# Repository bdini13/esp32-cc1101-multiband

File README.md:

# ESP32 + CC1101 Multiband

A custom USB-C development board combining an **ESP32-WROOM-32E-N8** with an
integrated **CC1101** sub-GHz radio, software-selected RF paths, and a vertical
SMA antenna connector at the opposite end from USB-C.

**Rev A3 · Fully connected review candidate · Not approved to manufacture or sell**

The aim is to replace a separate ESP32 board, CC1101 breakout and jumper wires
with one purpose-built PCB. The first intended build is **five assembled
engineering prototypes**, after the pre-order checks are complete. Possible
product sales are a future option, not a launch announcement.

## Current design

*KiCad design render—not a photograph of a built board. USB, SMA and some
RF parts lack complete 3D bodies. Their absence in the image does not mean
they were removed from the design.*

<details>
<summary>Top view and experimental routing</summary>

*The routing image is a separate experimental candidate, not the main placement
file or a fabrication package. Bottom and inner routes are not shown here.*

</details>

[Schematic SVG](output/svg-A3/esp32-cc1101-multiband.svg) ·
[Latest design report](reports/autonomous-refinement-A3-2026-09-26.md) ·
[Draft BOM](hardware/bom-draft.csv) · [Roadmap](ROADMAP.md)

Latest work: A3 replaces the power supply and RF switches, completes routed
connectivity, adds safe RF boot sequencing and proposes all populated parts.
See [engineering decisions and first-power instructions](docs/06-A3-prototype-engineering.md)
and the [pre-order blocker report](reports/preflight-A3.json). The crystal was
relocated and rerouted: all 180 artifact checks and six route screens now pass.
Independent/supplier reviews remain pending. No hardware has been tested.
Do not order historical A2 files.

## Building blocks and design inputs

### ESP32-WROOM-32E-N8 — controller and 2.4 GHz connectivity

*Stock module reference image: Espressif, linked from the manufacturer's site.
This is not a photo of the custom board or a guarantee of the N8 marking.*

The actual component is an Espressif module, not an entire stock development
board soldered onto another PCB. The selected N8 variant has 8 MB flash; its
ESP32 provides a dual-core processor, 2.4 GHz Wi-Fi and Bluetooth. Its PCB
antenna is separate from the sub-GHz SMA path. The antenna section extends
beyond the custom base board to preserve its keepout.
[Module datasheet](https://documentation.espressif.com/esp32-wroom-32e_esp32-wroom-32ue_datasheet_en.html).

Power/programming uses ESP32 development-board conventions: USB-to-UART,
automatic reset/boot control and manual BOOT/RESET buttons. This is not a
pin-compatible clone of a particular commercial DevKit.
[Espressif ESP32-DevKitC reference](https://docs.espressif.com/projects/esp-dev-kits/en/latest/esp32/esp32-devkitc/user_guide.html).

### Texas Instruments CC1101 — sub-GHz transceiver

*Representative package image: Texas Instruments. This is the IC package,
not a complete CC1101 antenna module; package markings may differ.*

The PCB integrates **CC1101RGPR** directly, with its crystal, bypass capacitors,
balun, switches and matching/filter components. TI specifies tuning ranges
of 300–348, 387–464 and 779–928 MHz. That does **not** make every frequency or
antenna equally usable or establish this board's RF performance.
[CC1101 product information and datasheet](https://www.ti.com/product/CC1101).

The separate [Amazon CC1101 module](https://a.co/d/01gplHzS) supplied by the
owner was a functional starting point. Its exact internal circuit and advertised
four-band performance have not been independently verified here. The switched
RF topology and initial component values also reference the
[M5Stack Cap CC1101 schematic](https://docs.m5stack.com/en/cap/Cap_CC1101).
This is a different implementation, not an endorsed M5Stack product.

### Supporting parts currently selected

| Function | Current design choice |
|---|---|
| USB-C | HRO TYPE-C-31-M-12, USB 2.0 connection |
| USB-to-UART | Silicon Labs CP2102N-A02-GQFN24 |
| 3.3 V regulator | AP63203WU-7 buck, XAL4030 4.7 uH inductor |
| USB startup / UART isolation | TPS22918, SN74LVC2G125; J4 ships unjumpered |
| Radio reference | Abracon ABM8, 26 MHz; load requires validation |
| RF selection | Two pSemi PE42442A-Z SP4T switches; three paths used |
| RF balun | B0310J50100AHF |
| Antenna connector | Amphenol 132134, vertical standard SMA female, 50 ohm |

See [third-party notices](THIRD_PARTY_NOTICES.md) for provenance, image credits
and license boundaries. Parts remain subject to sourcing, footprint and assembly
approval; the BOM is not an approved shopping list.

## Planned capabilities and features

| Feature | Planned behavior | Status |
|---|---|---|
| Four target bands | 315 / 433 / 868 / 915 MHz, one selected at a time | Not RF-validated |
| Software band switching | GPIO-operated RF switches; no DIP switches | Circuit present; firmware isolation only |
| Three RF branches | Dedicated 315 and 433 paths; shared 868/915 path | Matching, loss and isolation unmeasured |
| Single sub-GHz SMA | Vertical connector opposite USB-C | Placed; mechanical approval pending |
| USB-C power/programming | 5 V input, USB-to-UART flashing/logging | Captured; not bench-tested |
| Wi-Fi / Bluetooth | Available through the ESP32 module | Application integration planned |
| Developer controls | BOOT, RESET, LEDs and test pads | Included in draft |
| Expansion | Optional DNP 10-pin header | Included in draft |
| PCB | 90 × 36 mm base, four layers, nominal 1.6 mm | Stackup/impedance release pending |
| Safe bring-up | RF paths isolated; no transmit command | Implemented in initial firmware |

Band switching changes the **hardware path**. Future firmware must also set the
radio frequency/modem registers and operating limits. One CC1101 cannot listen
on all four bands simultaneously. Use an antenna suitable for the selected
band; a shared SMA does not imply a universal antenna.

There is no native USB, USB-PD, battery charger, finished RF application or
guaranteed protocol compatibility in this revision.

## What has actually been checked?

Snapshot: **2026-09-26**, KiCad 10.0.6. Design-file checks, not lab results.

| Check | Result |
|---|---|
| Schematic ERC | 0 reported violations |
| Main placement seed DRC | 0 violations; 283 unconnected items (not the routed board) |
| Targeted artifact checks | **180 / 180 passing** on refined candidate / explicit seed checks |
| Added route screens | **6 / 6 passing**; oscillator routing, cross-layer clearance and modeled DC drops |
| Separate A3 routed candidate DRC | **0 violations; 0 unconnected items** |
| Fresh schematic / routed PCB comparison | Every numbered pad net, value and footprint name matches |
| Layer constraints | No signal traces on In1; RF/clock top-only; documented USB crossover |
| Candidate power routing | Main rails explicitly routed; 60 narrower branch/neck segments listed; critical copper paths quantitatively screened |
| Parts selection | **94 / 94** populated positions have proposed exact parts; sourcing unapproved |
| Physical boards tested | **None** |

Zero reported violations does not prove working or compliant hardware. A3's
power redesign addresses the earlier LDO heat problem and the new switches
cover the target bands in their specified frequency range. Actual power
sequencing, temperature, impedance, matching and crystal startup/frequency
remain unmeasured. C21 and U5 contain in-pad vias requiring filled/capped
processing; supplier DFM confirmation is mandatory. USB power must be
configured before fitting J4, and full combined Wi-Fi/radio load is not approved.

[Raw reports](reports/) · [Verification checklist](docs/04-verification-plan.md) ·
[Power, routing and RF validation plan](docs/06-A3-prototype-engineering.md)

## Roadmap

1. **Design capture — substantially complete:** schematic, placement, draft
   BOM, local footprints, bring-up firmware and automated checks.
2. **Prototype review — in progress:** routed connectivity and proposed parts
   complete; crystal, power, mechanical, supplier and independent review open.
3. **Five-board build — not ordered:** reviewed fabrication and assembly files,
   then separately approved prototype procurement.
4. **Bench and RF tuning — not started:** power/temperature, USB, crystal,
   per-band matching, harmonics and receive performance.
5. **Firmware/application — planned:** validated receive-first operation,
   controlled band changes and deliberately configured regional limits.
6. **Possible product — undecided:** hardware revision, compliance, enclosure,
   test fixtures, sourcing, support and commercial terms.

The [detailed roadmap](ROADMAP.md) uses acceptance criteria, not promised dates.
There is no release date, sales price, preorder or claim of certification.

## Open the project

Open `hardware/esp32-cc1101-multiband.kicad_pro` in **KiCad 10** for the main
placement seed and schematic. Open `hardware/A3-routing-candidate.kicad_pro`
separately for the unapproved routing experiment. Do not order either one.

Python generators are the editable source for this checkpoint. **Regenerating
placement overwrites the generated board; preserve manual routing first.**
See [rebuild instructions](hardware/REBUILD.md) and
[firmware instructions](firmware/bringup/README.md).

Initial firmware resets the CC1101, checks repeated PARTNUM/VERSION reads and
stable IDLE state, and logs explicit failures. It does not configure a receiver
or transmitter and has not run on physical hardware. Passing digital diagnostics
is not proof of authenticity or RF qualification.

## AI disclosure

This project is developed with substantial assistance from **OpenAI Codex**
under the owner's direction. AI assisted with component research, schematic/PCB
generators, footprints, experimental routing, firmware, documentation and review.
Design images are KiCad renders/exports, not AI-generated product photographs.

AI output and automated checks can contain errors. They are not independent
engineering approval, bench validation or regulatory certification. No physical
prototype has been completed. Qualified human electrical/RF review remains a
release gate. See the [full AI disclosure](AI_DISCLOSURE.md).

## Licensing, commercial plans and safety

This initial publication uses the **[Public Review License](LICENSE)**:
non-commercial study/private evaluation is permitted; manufacturing, product
sales and other uses beyond its limited permissions require written permission.
Commercial rights are reserved while the owner's plans are undecided. This is
**source-available, not open-source/open hardware**. Third-party terms are
separate; see [notices](THIRD_PARTY_NOTICES.md). Obtain legal advice before
relying on the custom license for a commercial launch.

Use only with equipment and signals you own or are authorized to test. Tunable
frequencies are not automatically permitted transmit frequencies. Final use and
sale require applicable RF, EMC, product-safety and other compliance work. This
prototype is not for safety-critical applications. No manufacturer named here
endorses the project.

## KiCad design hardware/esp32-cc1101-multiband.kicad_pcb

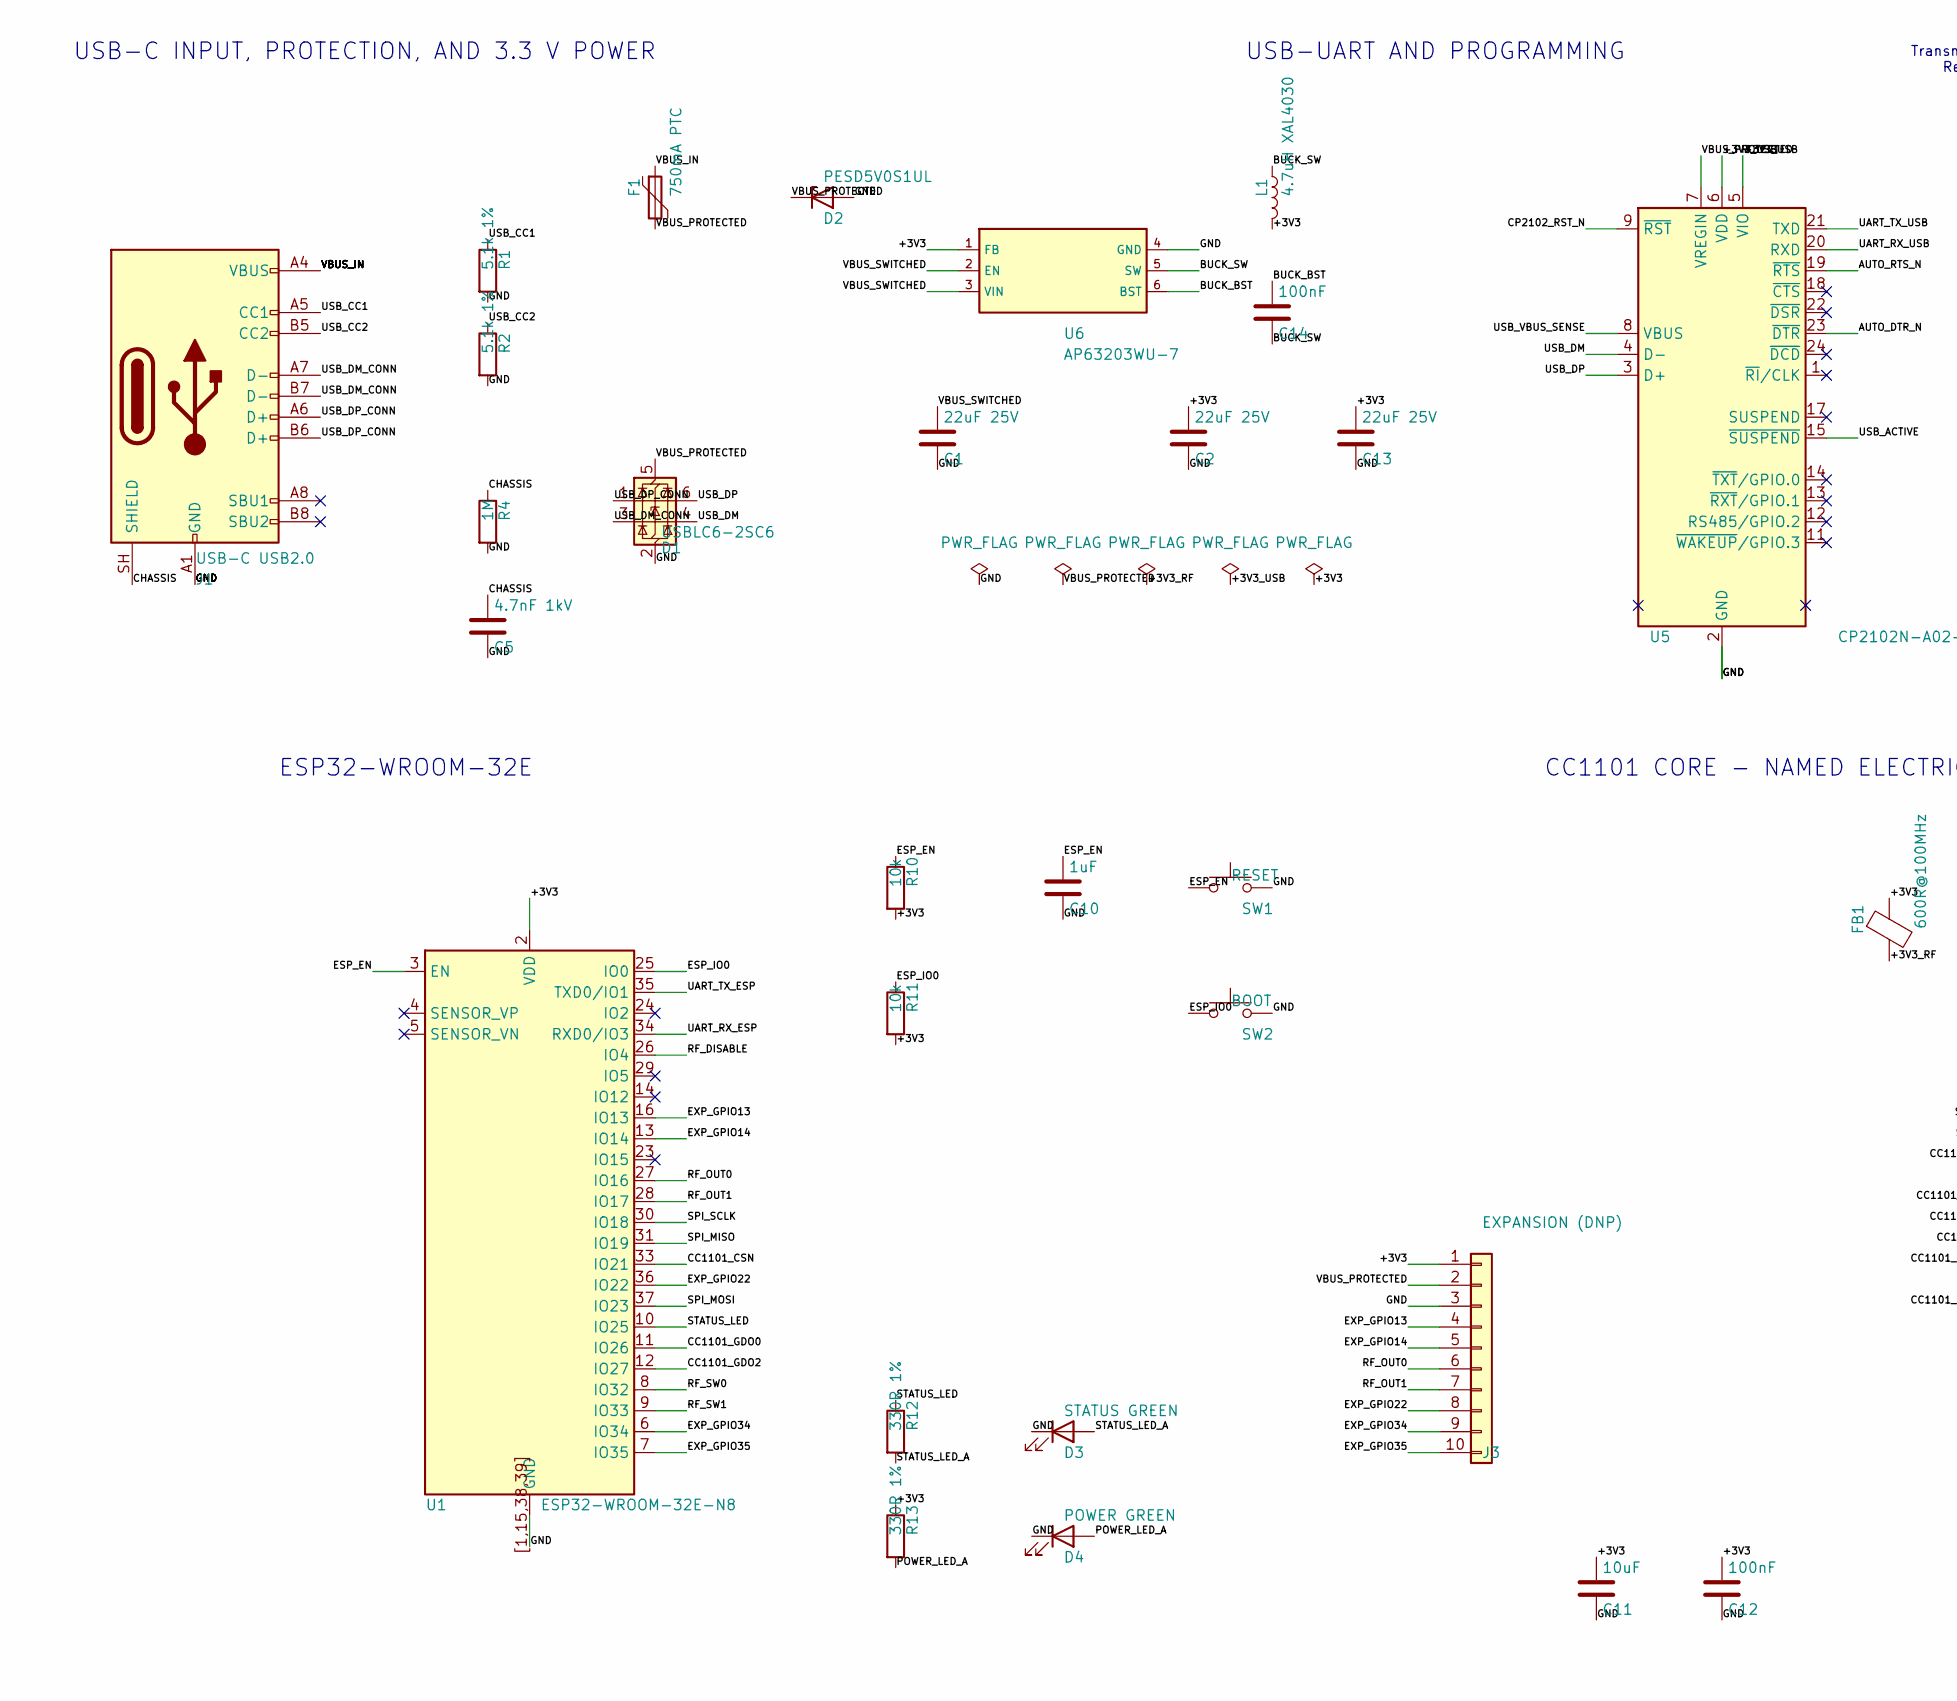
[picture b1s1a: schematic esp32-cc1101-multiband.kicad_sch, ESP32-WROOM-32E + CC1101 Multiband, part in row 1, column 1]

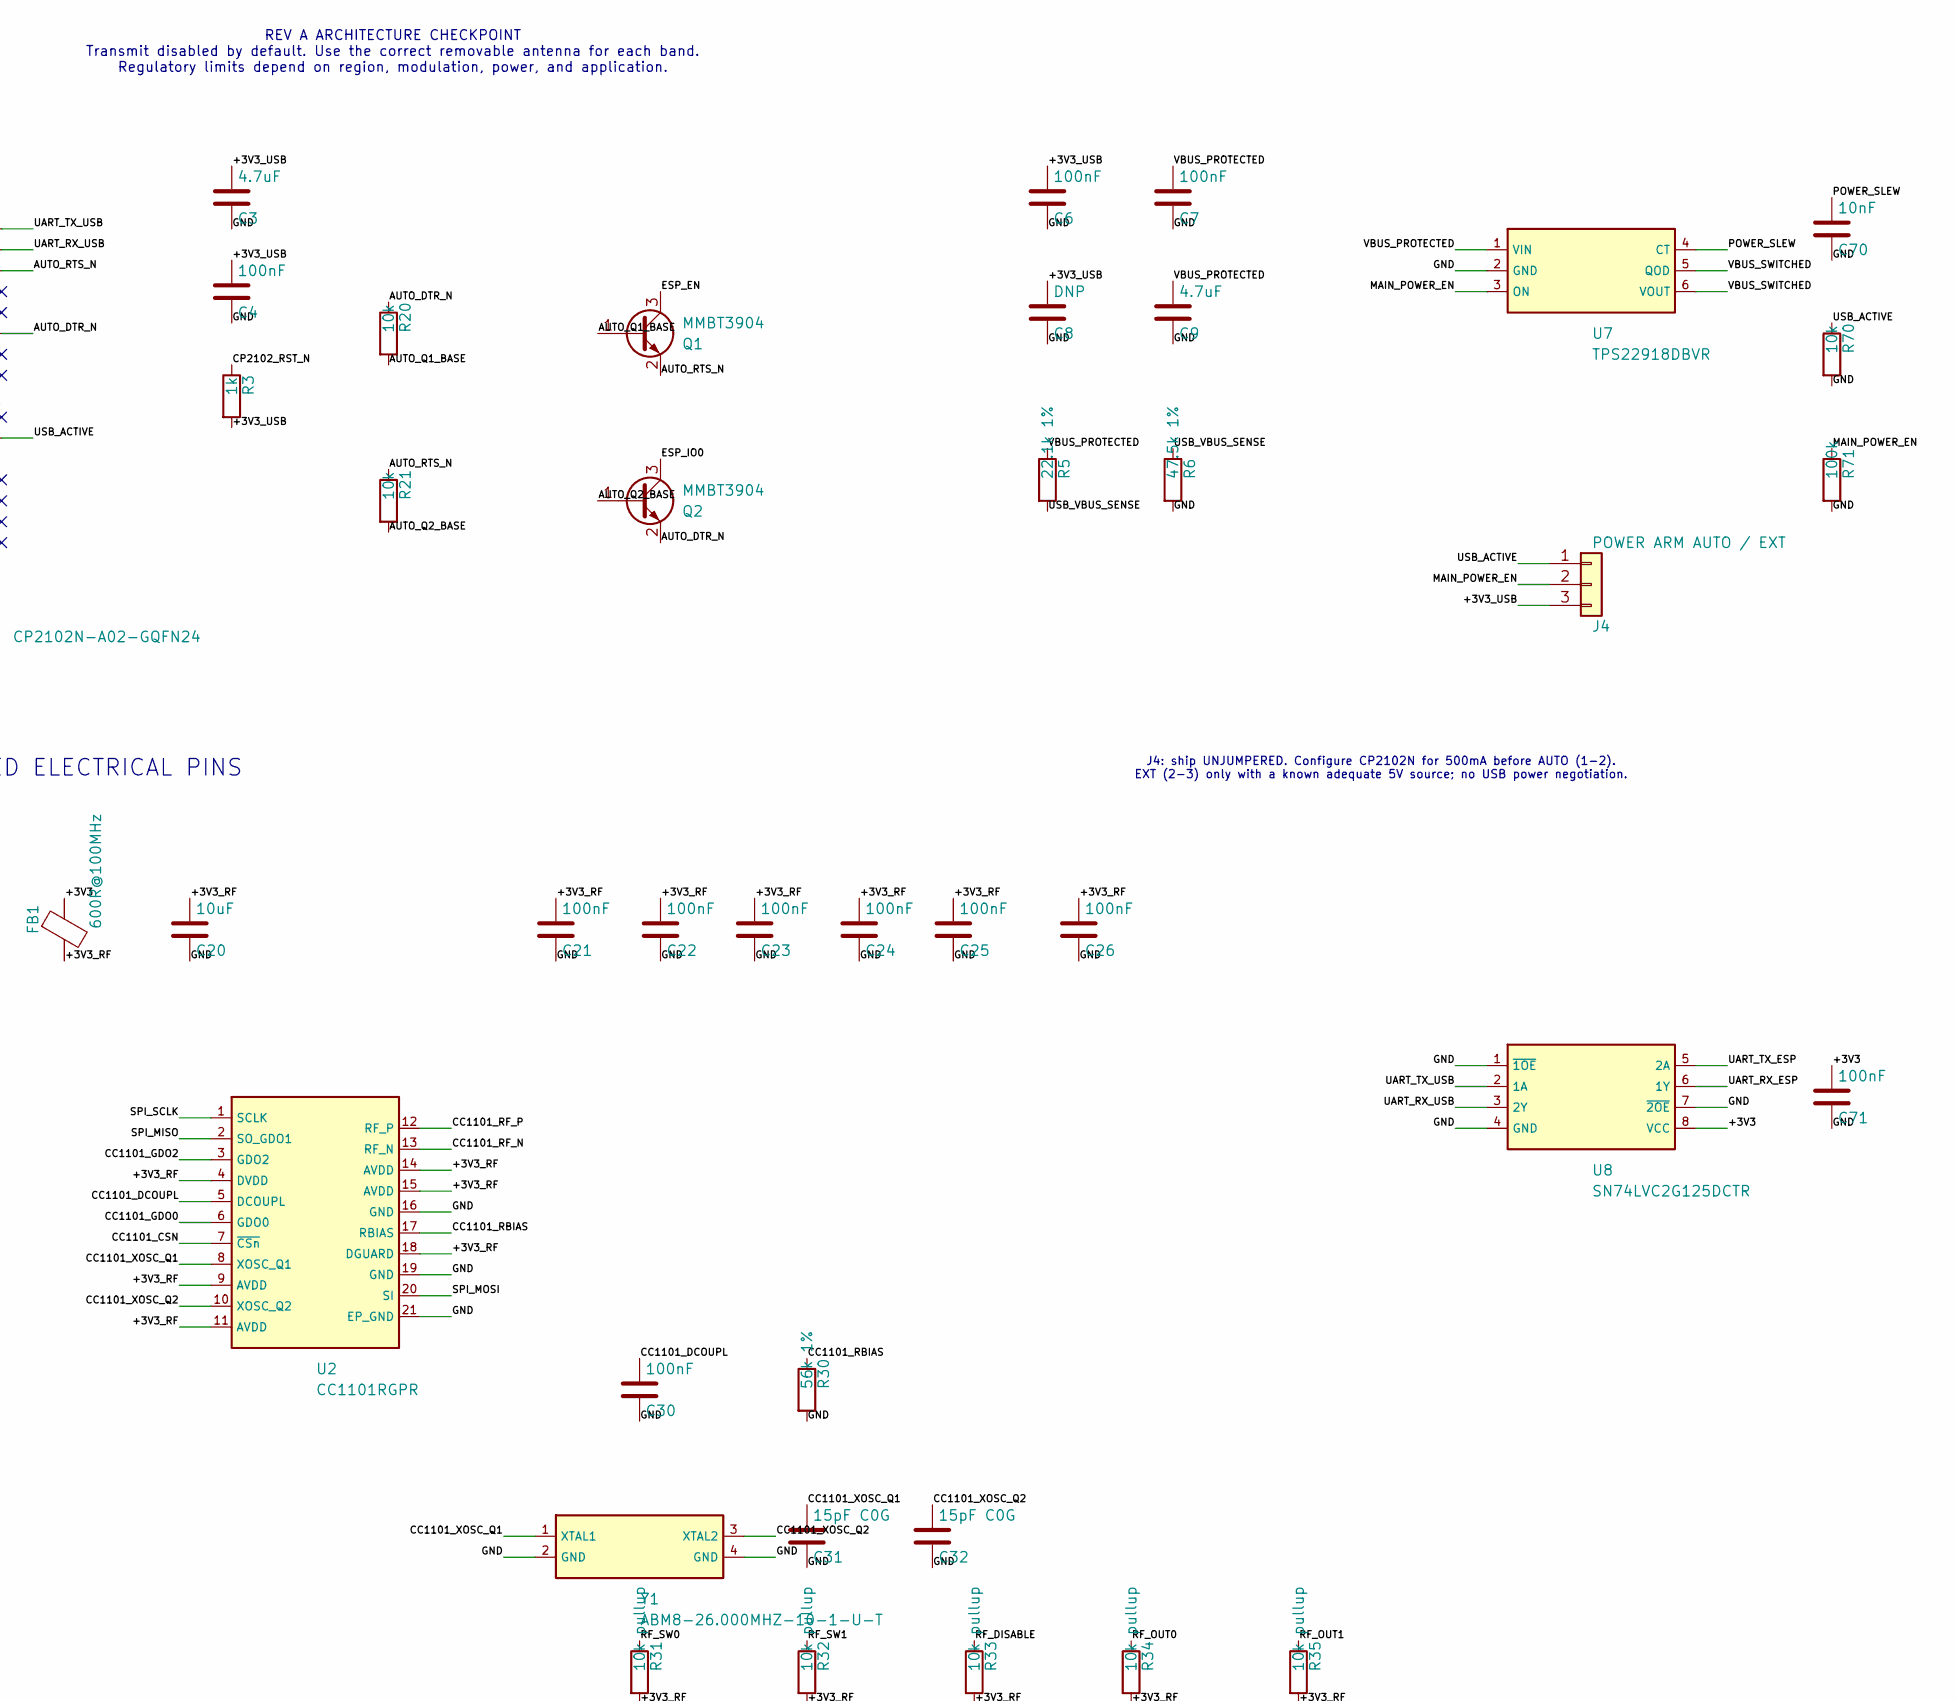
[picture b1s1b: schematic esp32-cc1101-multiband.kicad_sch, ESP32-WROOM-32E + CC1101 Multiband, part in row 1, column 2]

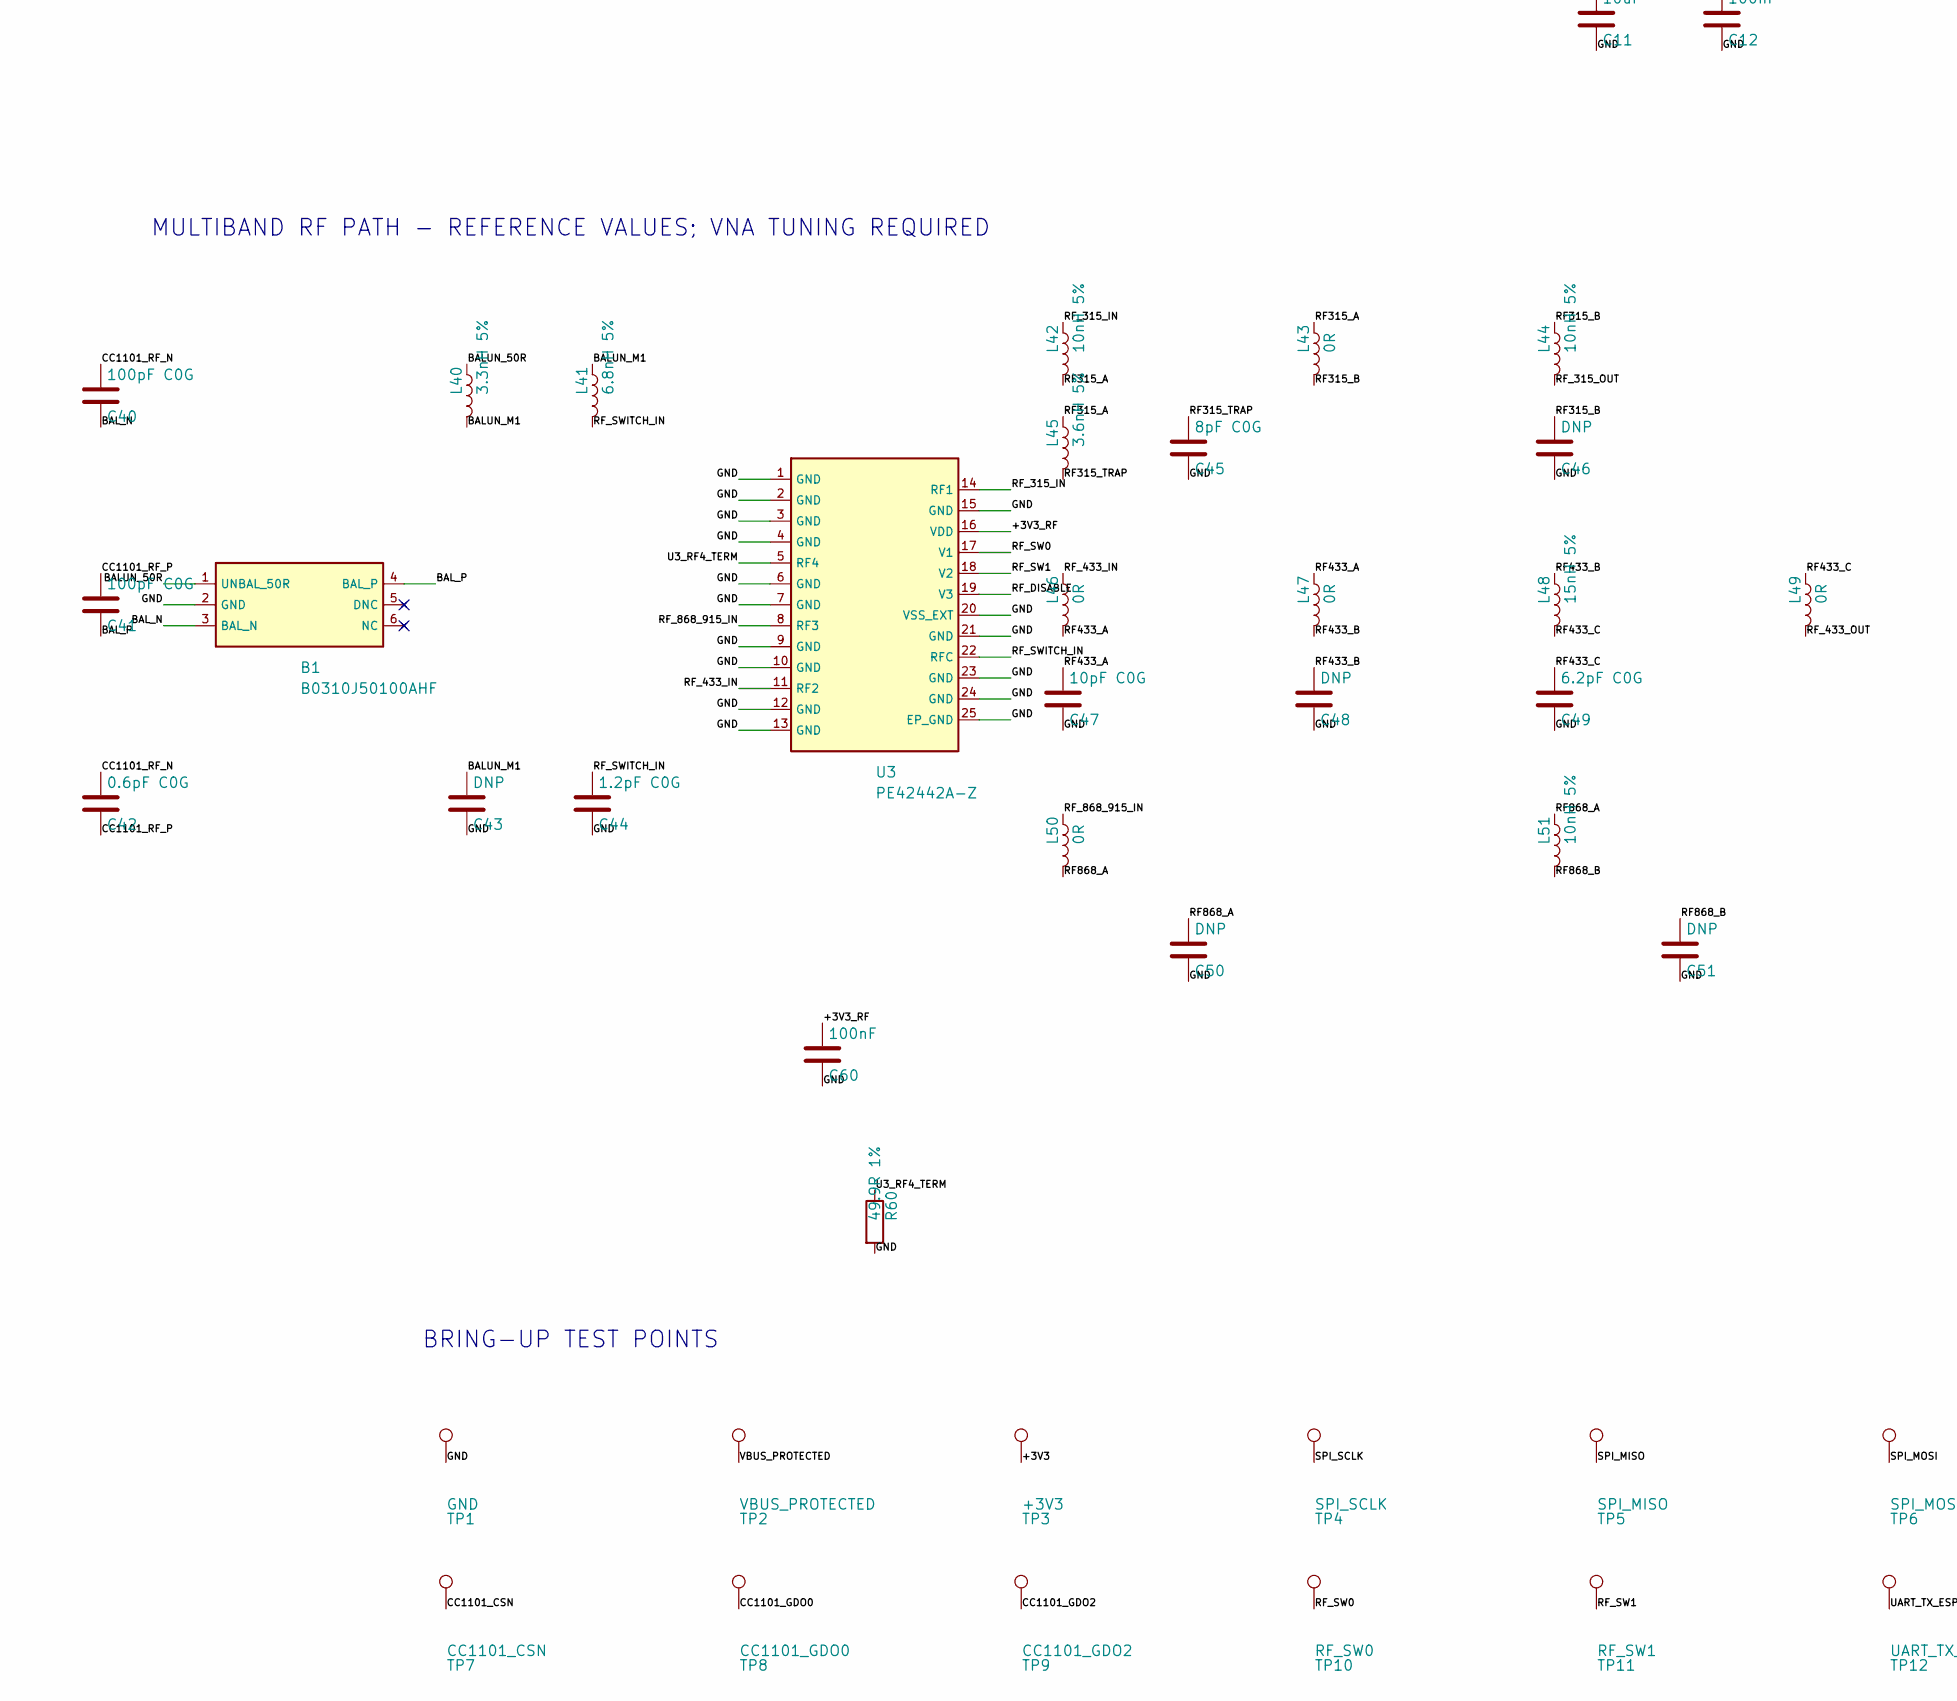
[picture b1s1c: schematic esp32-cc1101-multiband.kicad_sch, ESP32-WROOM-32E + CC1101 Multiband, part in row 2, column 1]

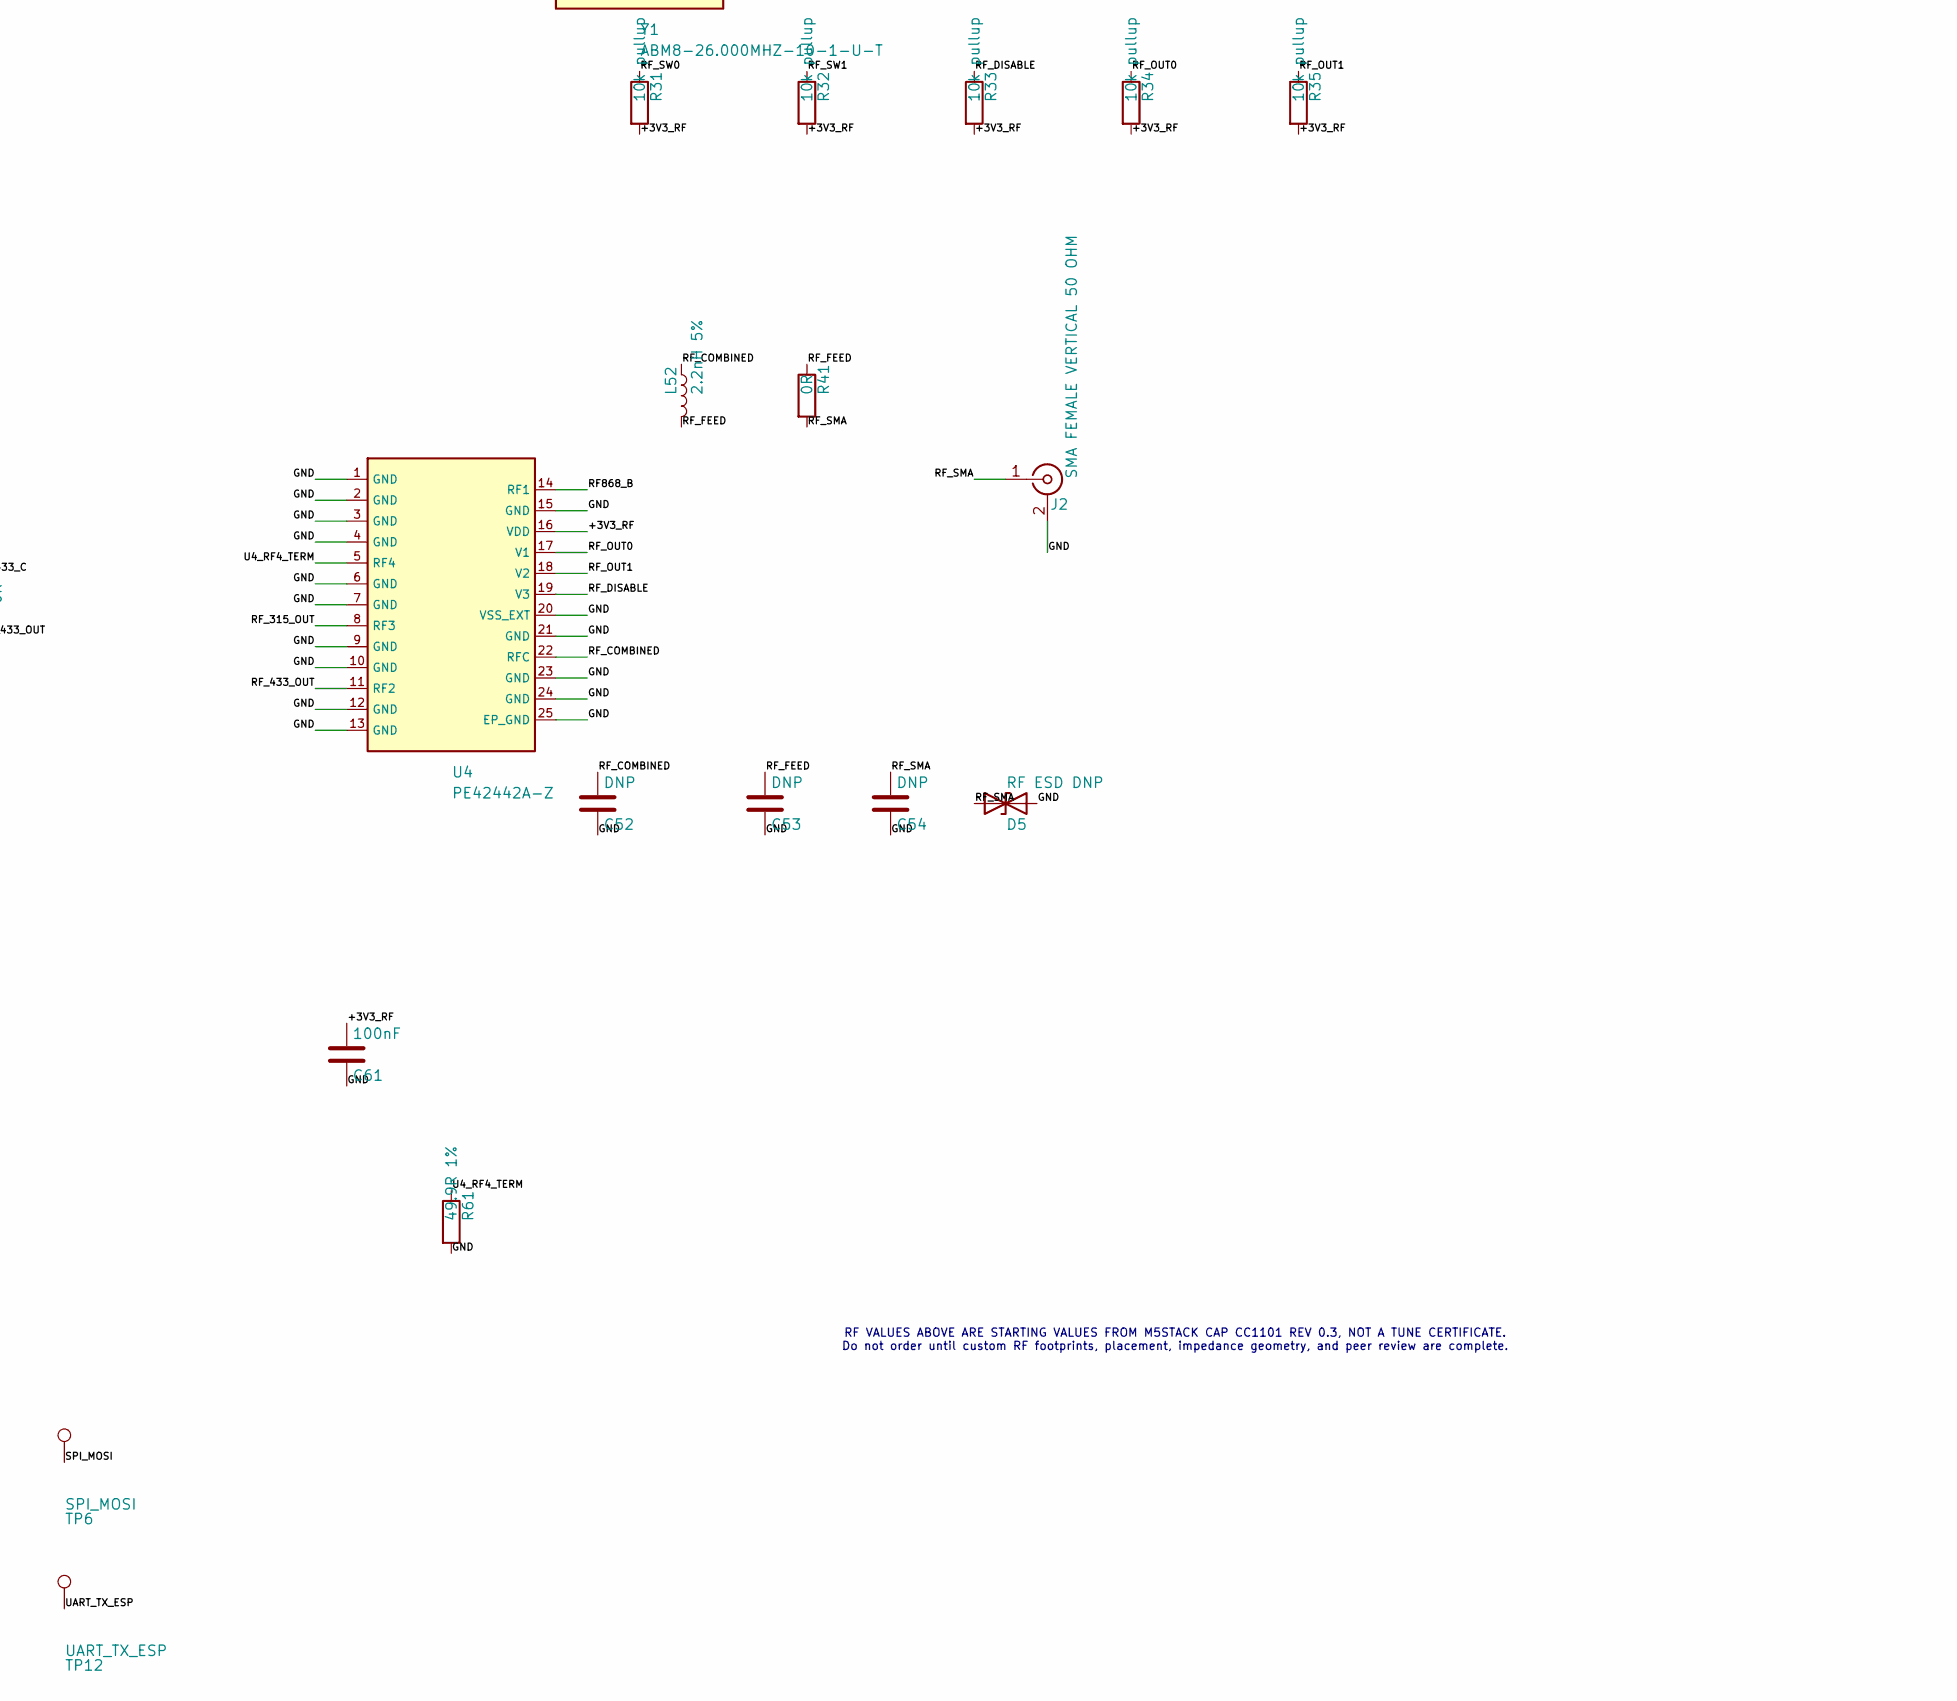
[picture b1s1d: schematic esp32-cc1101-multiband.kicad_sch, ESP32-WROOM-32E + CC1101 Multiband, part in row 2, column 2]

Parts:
B1: B0310J50100AHF; TTM_B0310J50100AHF
C1, C2, C13: 22uF 25V; C_1206_3216Metric
C3, C9: 4.7uF; C_0603_1608Metric
C4, C6, C7, C12, C14, C21, C22, C23, C24, C25, C26, C30, C60, C61, C71: 100nF; C_0402_1005Metric
C5: 4.7nF 1kV; C_1206_3216Metric
C8: DNP; C_0603_1608Metric
C10: 1uF; C_0603_1608Metric
C11, C20: 10uF; C_0603_1608Metric
C31, C32: 15pF C0G; C_0402_1005Metric
C40, C41: 100pF C0G; C_0402_1005Metric
C42: 0.6pF C0G; C_0402_1005Metric
C43, C46, C48, C50, C51, C52, C53, C54: DNP; C_0402_1005Metric
C44: 1.2pF C0G; C_0402_1005Metric
C45: 8pF C0G; C_0402_1005Metric
C47: 10pF C0G; C_0402_1005Metric
C49: 6.2pF C0G; C_0402_1005Metric
C70: 10nF; C_0402_1005Metric
D1: USBLC6-2SC6; SOT-23-6
D2: PESD5V0S1UL; D_SOD-882
D3: STATUS GREEN; LED_0603_1608Metric
D4: POWER GREEN; LED_0603_1608Metric
D5: RF ESD DNP; D_0402_1005Metric
F1: 750mA PTC; Fuse_1206_3216Metric
FB1: 600R@100MHz; L_0603_1608Metric
J1: USB-C USB2.0; USB_C_Receptacle_HRO_TYPE-C-31-M-12
J2: SMA FEMALE VERTICAL 50 OHM; SMA_Amphenol_132134_Vertical
J3: EXPANSION (DNP); PinHeader_1x10_P2.54mm_Vertical
J4: POWER ARM AUTO / EXT; PinHeader_1x03_P2.54mm_Vertical
L1: 4.7uH XAL4030; L_Coilcraft_XAL4030-XXX
L40: 3.3nH 5%; L_0402_1005Metric
L41: 6.8nH 5%; L_0402_1005Metric
L42, L44, L51: 10nH 5%; L_0402_1005Metric
L43, L46, L47, L49, L50: 0R; L_0402_1005Metric
L45: 3.6nH 5%; L_0402_1005Metric
L48: 15nH 5%; L_0402_1005Metric
L52: 2.2nH 5%; L_0402_1005Metric
PWR1, PWR2, PWR3, PWR4, PWR5: PWR_FLAG
Q1, Q2: MMBT3904; SOT-23
R1, R2: 5.1k 1%; R_0603_1608Metric
R3: 1k; R_0603_1608Metric
R4: 1M; R_0603_1608Metric
R5: 22.1k 1%; R_0603_1608Metric
R6: 47.5k 1%; R_0603_1608Metric
R10, R11, R20, R21, R70: 10k; R_0603_1608Metric
R12, R13: 330R 1%; R_0603_1608Metric
R30: 56k 1%; R_0402_1005Metric
R31, R32, R33, R34, R35: 10k pullup; R_0603_1608Metric
R41: 0R; R_0402_1005Metric
R60, R61: 49.9R 1%; R_0402_1005Metric
R71: 100k; R_0603_1608Metric
SW1: RESET; SW_Push_1P1T_NO_CK_KMR2
SW2: BOOT; SW_Push_1P1T_NO_CK_KMR2
TP1: GND; TestPoint_Pad_D1.0mm
TP2: VBUS_PROTECTED; TestPoint_Pad_D1.0mm
TP3: +3V3; TestPoint_Pad_D1.0mm
TP4: SPI_SCLK; TestPoint_Pad_D1.0mm
TP5: SPI_MISO; TestPoint_Pad_D1.0mm
TP6: SPI_MOSI; TestPoint_Pad_D1.0mm
TP7: CC1101_CSN; TestPoint_Pad_D1.0mm
TP8: CC1101_GDO0; TestPoint_Pad_D1.0mm
TP9: CC1101_GDO2; TestPoint_Pad_D1.0mm
TP10: RF_SW0; TestPoint_Pad_D1.0mm
TP11: RF_SW1; TestPoint_Pad_D1.0mm
TP12: UART_TX_ESP; TestPoint_Pad_D1.0mm
U1: ESP32-WROOM-32E-N8; ESP32-WROOM-32E
U2: CC1101RGPR; Texas_RGP0020H_VQFN-20-1EP_4x4mm_P0.5mm_EP2.4x2.4mm_Thermal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
U3, U4: PE42442A-Z; pSemi_PE42442_QFN24
U5: CP2102N-A02-GQFN24; QFN-24-1EP_4x4mm_P0.5mm_EP2.6x2.6mm
U6: AP63203WU-7; Diodes_TSOT26
U7: TPS22918DBVR; SOT-23-6
U8: SN74LVC2G125DCTR; SSOP-8_2.95x2.8mm_P0.65mm
Y1: ABM8-26.000MHZ-10-1-U-T; Abracon_ABM8_4Pin_3.2x2.5mm

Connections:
/+3V3: C2.1, C11.1, C12.1, C13.1, C71.1, FB1.1, J3.1, L1.2, PWR5.1, R10.2, R11.2, R13.1, TP3.1, U1.2 (VDD), U6.1 (FB), U8.8 (VCC)
/+3V3_RF: C20.1, C21.1, C22.1, C23.1, C24.1, C25.1, C26.1, C60.1, C61.1, FB1.2, PWR3.1, R31.2, R32.2, R33.2, R34.2, R35.2, U2.4 (DVDD), U2.9 (AVDD), U2.11 (AVDD), U2.14 (AVDD), U2.15 (AVDD), U2.18 (DGUARD), U3.16 (VDD), U4.16 (VDD)
/+3V3_USB: C3.1, C4.1, C6.1, C8.1, J4.3, PWR4.1, R3.2, U5.5 (VIO), U5.6 (VDD)
/AUTO_DTR_N: Q2.2 (E), R20.1, U5.23 (~DTR)
/AUTO_Q1_BASE: Q1.1 (B), R20.2
/AUTO_Q2_BASE: Q2.1 (B), R21.2
/AUTO_RTS_N: Q1.2 (E), R21.1, U5.19 (~RTS)
/BALUN_50R: B1.1 (UNBAL_50R), L40.1
/BALUN_M1: C43.1, L40.2, L41.1
/BAL_N: B1.3 (BAL_N), C40.2
/BAL_P: B1.4 (BAL_P), C41.2
/BUCK_BST: C14.1, U6.6 (BST)
/BUCK_SW: C14.2, L1.1, U6.5 (SW)
/CC1101_CSN: TP7.1, U1.33 (IO21), U2.7 (~CSn)
/CC1101_DCOUPL: C30.1, U2.5 (DCOUPL)
/CC1101_GDO0: TP8.1, U1.11 (IO26), U2.6 (GDO0)
/CC1101_GDO2: TP9.1, U1.12 (IO27), U2.3 (GDO2)
/CC1101_RBIAS: R30.1, U2.17 (RBIAS)
/CC1101_RF_N: C40.1, C42.1, U2.13 (RF_N)
/CC1101_RF_P: C41.1, C42.2, U2.12 (RF_P)
/CC1101_XOSC_Q1: C31.1, U2.8 (XOSC_Q1), Y1.1 (XTAL1)
/CC1101_XOSC_Q2: C32.1, U2.10 (XOSC_Q2), Y1.3 (XTAL2)
/CHASSIS: C5.1, J1.SH (SHIELD), R4.1
/CP2102_RST_N: R3.1, U5.9 (~RST)
/ESP_EN: C10.1, Q1.3 (C), R10.1, SW1.1, U1.3 (EN)
/ESP_IO0: Q2.3 (C), R11.1, SW2.1, U1.25 (IO0)
/EXP_GPIO13: J3.4, U1.16 (IO13)
/EXP_GPIO14: J3.5, U1.13 (IO14)
/EXP_GPIO22: J3.8, U1.36 (IO22)
/EXP_GPIO34: J3.9, U1.6 (IO34)
/EXP_GPIO35: J3.10, U1.7 (IO35)
/GND: B1.2 (GND), C1.2, C2.2, C3.2, C4.2, C5.2, C6.2, C7.2, C8.2, C9.2, C10.2, C11.2, C12.2, C13.2, C20.2, C21.2, C22.2, C23.2, C24.2, C25.2, C26.2, C30.2, C31.2, C32.2, C43.2, C44.2, C45.2, C46.2, C47.2, C48.2, C49.2, C50.2, C51.2, C52.2, C53.2, C54.2, C60.2, C61.2, C70.2, C71.2, D1.2 (GND), D2.2 (A), D3.1 (K), D4.1 (K), D5.2 (A2), J1.A1 (GND), J1.A12 (GND), J1.B1 (GND), J1.B12 (GND), J2.2 (Ext), J3.3, PWR1.1, R1.2, R2.2, R4.2, R6.2, R30.2, R60.2, R61.2, R70.2, R71.2, SW1.2, SW2.2, TP1.1, U1.1, U1.15, U1.38, U1.39, U1.[1,15,38,39] (GND), U2.16 (GND), U2.19 (GND), U2.21 (EP_GND), U3.1 (GND), U3.2 (GND), U3.3 (GND), U3.4 (GND), U3.6 (GND), U3.7 (GND), U3.9 (GND), U3.10 (GND), U3.12 (GND), U3.13 (GND), U3.15 (GND), U3.20 (VSS_EXT), U3.21 (GND), U3.23 (GND), U3.24 (GND), U3.25 (EP_GND), U4.1 (GND), U4.2 (GND), U4.3 (GND), U4.4 (GND), U4.6 (GND), U4.7 (GND), U4.9 (GND), U4.10 (GND), U4.12 (GND), U4.13 (GND), U4.15 (GND), U4.20 (VSS_EXT), U4.21 (GND), U4.23 (GND), U4.24 (GND), U4.25 (EP_GND), U5.2 (GND), U5.25 (GND), U6.4 (GND), U7.2 (GND), U8.1 (~1OE), U8.4 (GND), U8.7 (~2OE), Y1.2 (GND), Y1.4 (GND)
/MAIN_POWER_EN: J4.2, R71.1, U7.3 (ON)
/POWER_LED_A: D4.2 (A), R13.2
/POWER_SLEW: C70.1, U7.4 (CT)
/RF315_A: L42.2, L43.1, L45.1
/RF315_B: C46.1, L43.2, L44.1
/RF315_TRAP: C45.1, L45.2
/RF433_A: C47.1, L46.2, L47.1
/RF433_B: C48.1, L47.2, L48.1
/RF433_C: C49.1, L48.2, L49.1
/RF868_A: C50.1, L50.2, L51.1
/RF868_B: C51.1, L51.2, U4.14 (RF1)
/RF_315_IN: L42.1, U3.14 (RF1)
/RF_315_OUT: L44.2, U4.8 (RF3)
/RF_433_IN: L46.1, U3.11 (RF2)
/RF_433_OUT: L49.2, U4.11 (RF2)
/RF_868_915_IN: L50.1, U3.8 (RF3)
/RF_COMBINED: C52.1, L52.1, U4.22 (RFC)
/RF_DISABLE: R33.1, U1.26 (IO4), U3.19 (V3), U4.19 (V3)
/RF_FEED: C53.1, L52.2, R41.1
/RF_OUT0: J3.6, R34.1, U1.27 (IO16), U4.17 (V1)
/RF_OUT1: J3.7, R35.1, U1.28 (IO17), U4.18 (V2)
/RF_SMA: C54.1, D5.1 (A1), J2.1 (In), R41.2
/RF_SW0: R31.1, TP10.1, U1.8 (IO32), U3.17 (V1)
/RF_SW1: R32.1, TP11.1, U1.9 (IO33), U3.18 (V2)
/RF_SWITCH_IN: C44.1, L41.2, U3.22 (RFC)
/SPI_MISO: TP5.1, U1.31 (IO19), U2.2 (SO_GDO1)
/SPI_MOSI: TP6.1, U1.37 (IO23), U2.20 (SI)
/SPI_SCLK: TP4.1, U1.30 (IO18), U2.1 (SCLK)
/STATUS_LED: R12.1, U1.10 (IO25)
/STATUS_LED_A: D3.2 (A), R12.2
/U3_RF4_TERM: R60.1, U3.5 (RF4)
/U4_RF4_TERM: R61.1, U4.5 (RF4)
/UART_RX_ESP: U1.34 (RXD0/IO3), U8.6 (1Y)
/UART_RX_USB: U5.20 (RXD), U8.3 (2Y)
/UART_TX_ESP: TP12.1, U1.35 (TXD0/IO1), U8.5 (2A)
/UART_TX_USB: U5.21 (TXD), U8.2 (1A)
/USB_ACTIVE: J4.1, R70.1, U5.15 (~SUSPEND)
/USB_CC1: J1.A5 (CC1), R1.1
/USB_CC2: J1.B5 (CC2), R2.1
/USB_DM: D1.4 (I/O2), U5.4 (D-)
/USB_DM_CONN: D1.3 (I/O2), J1.A7 (D-), J1.B7 (D-)
/USB_DP: D1.6 (I/O1), U5.3 (D+)
/USB_DP_CONN: D1.1 (I/O1), J1.A6 (D+), J1.B6 (D+)
/USB_VBUS_SENSE: R5.2, R6.1, U5.8 (VBUS)
/VBUS_IN: F1.1, J1.A4 (VBUS), J1.A9 (VBUS), J1.B4 (VBUS), J1.B9 (VBUS)
/VBUS_PROTECTED: C7.1, C9.1, D1.5 (VBUS), D2.1 (K), F1.2, J3.2, PWR2.1, R5.1, TP2.1, U5.7 (VREGIN), U7.1 (VIN)
/VBUS_SWITCHED: C1.1, U6.2 (EN), U6.3 (VIN), U7.5 (QOD), U7.6 (VOUT)

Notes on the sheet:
USB-C INPUT, PROTECTION, AND 3.3 V POWER
J4: ship UNJUMPERED. Configure CP2102N for 500mA before AUTO (1-2). EXT (2-3) only with a known adequate 5V source; no USB power negotiation.
USB-UART AND PROGRAMMING
ESP32-WROOM-32E
CC1101 CORE - NAMED ELECTRICAL PINS
MULTIBAND RF PATH - REFERENCE VALUES; VNA TUNING REQUIRED
RF VALUES ABOVE ARE STARTING VALUES FROM M5STACK CAP CC1101 REV 0.3, NOT A TUNE CERTIFICATE. Do not order until custom RF footprints, placement, impedance geometry, and peer review are complete.
REV A ARCHITECTURE CHECKPOINT Transmit disabled by default. Use the correct removable antenna for each band. Regulatory limits depend on region, modulation, power, and application.
BRING-UP TEST POINTS
